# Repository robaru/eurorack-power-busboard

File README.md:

# Eurorack Power Busboard

A passive power busboard for a Eurorack case, based on the
[Eurorack Power Breakout](https://github.com/moPsy-project/eurorack-power-breakout) by Stefan Haun
(moPsy project). I took Stefan KiCad project as a starting point and started playing around with it
to create the busboard to power my modules.

* 10 Eurorack power headers (2×8, with +5V, CV and Gate)
* Power input on a 4-pin WAGO screw terminal (+12V, GND, -12V, +5V)
* Basic filtering on each rail (ferrite bead, 100n and 10u)
* One LED per rail (+12V, -12V, +5V)
* Through-hole parts only, 190 × 31 mm, two M3 mounting holes

## Status

I built it and it works. Some things might need correcting, mostly the position of a few parts and
labels, so check the layout!

I have some spare PCBs. If you want one, get in touch!

## Files

* `eurorack-power-breakout.kicad_pro` / `.kicad_sch` / `.kicad_pcb`: KiCad project
* `eurorack-power-breakout-gerbers.zip`: Gerbers and drill files, ready to upload to a PCB fab
* `plots/`: the same Gerbers and drill files, unzipped
* `images/`: 3D renders (`board-3d.png`, `board-top.png`)
* `eurorack-power-breakout.csv`: bill of materials

## License

Licensed under [Creative Commons Attribution-ShareAlike 4.0 International](http://creativecommons.org/licenses/by-sa/4.0/),
like the original. Original design by Stefan Haun (mail@tuxathome.de), modified by Roberto
Barumerli. See [LICENSE.txt](LICENSE.txt).

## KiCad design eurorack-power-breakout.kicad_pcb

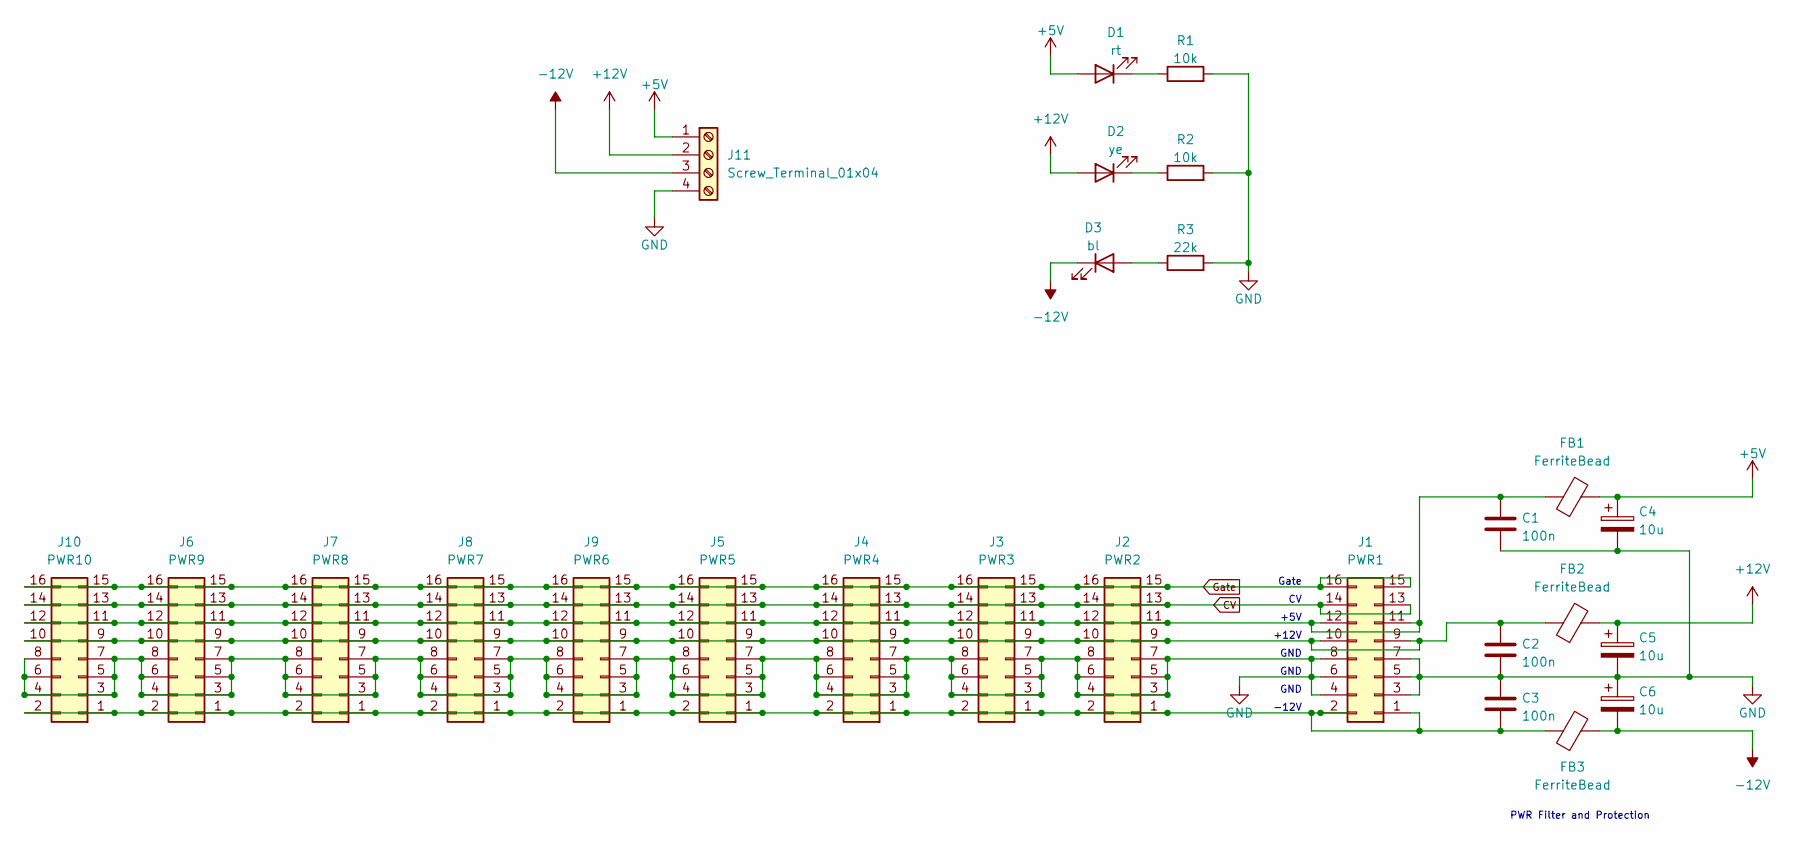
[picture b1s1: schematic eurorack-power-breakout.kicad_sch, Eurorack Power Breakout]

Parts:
C1, C2, C3: 100n; C_Disc_D4.3mm_W1.9mm_P5.00mm
C4, C5, C6: 10u; CP_Radial_D5.0mm_P2.50mm
D1: rt; LED_D3.0mm
D2: ye; LED_D3.0mm
D3: bl; LED_D3.0mm
FB1, FB2, FB3: FerriteBead; R_Axial_DIN0207_L6.3mm_D2.5mm_P7.62mm_Horizontal
J1: PWR1; PinHeader_2x08_P2.54mm_Vertical
J2: PWR2; PinHeader_2x08_P2.54mm_Vertical
J3: PWR3; PinHeader_2x08_P2.54mm_Vertical
J4: PWR4; PinHeader_2x08_P2.54mm_Vertical
J5: PWR5; PinHeader_2x08_P2.54mm_Vertical
J6: PWR9; PinHeader_2x08_P2.54mm_Vertical
J7: PWR8; PinHeader_2x08_P2.54mm_Vertical
J8: PWR7; PinHeader_2x08_P2.54mm_Vertical
J9: PWR6; PinHeader_2x08_P2.54mm_Vertical
J10: PWR10; PinHeader_2x08_P2.54mm_Vertical
J11: Screw_Terminal_01x04; TerminalBlock_WAGO_236-104_1x04_P5.00mm_45Degree
R1, R2: 10k; R_Axial_DIN0207_L6.3mm_D2.5mm_P2.54mm_Vertical
R3: 22k; R_Axial_DIN0207_L6.3mm_D2.5mm_P2.54mm_Vertical

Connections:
+5V: C4.1, D1.2 (A), FB1.2, J11.1
+12V: C5.1, D2.2 (A), FB2.2, J11.2
-12V: C6.2, D3.1 (K), FB3.2, J11.3
CV: J1.13, J1.14, J2.13, J2.14, J3.13, J3.14, J4.13, J4.14, J5.13, J5.14, J6.13, J6.14, J7.13, J7.14, J8.13, J8.14, J9.13, J9.14, J10.13, J10.14
GND: C1.2, C2.2, C3.1, C4.2, C5.2, C6.1, J1.3, J1.4, J1.5, J1.6, J1.7, J1.8, J2.3, J2.4, J2.5, J2.6, J2.7, J2.8, J3.3, J3.4, J3.5, J3.6, J3.7, J3.8, J4.3, J4.4, J4.5, J4.6, J4.7, J4.8, J5.3, J5.4, J5.5, J5.6, J5.7, J5.8, J6.3, J6.4, J6.5, J6.6, J6.7, J6.8, J7.3, J7.4, J7.5, J7.6, J7.7, J7.8, J8.3, J8.4, J8.5, J8.6, J8.7, J8.8, J9.3, J9.4, J9.5, J9.6, J9.7, J9.8, J10.3, J10.4, J10.5, J10.6, J10.7, J10.8, J11.4, R1.2, R2.2, R3.2
Gate: J1.15, J1.16, J2.15, J2.16, J3.15, J3.16, J4.15, J4.16, J5.15, J5.16, J6.15, J6.16, J7.15, J7.16, J8.15, J8.16, J9.15, J9.16, J10.15, J10.16
unnamed: D1.1 (K), R1.1
unnamed: D2.1 (K), R2.1
unnamed: D3.2 (A), R3.1
unnamed: C3.2, FB3.1, J1.1, J1.2, J2.1, J2.2, J3.1, J3.2, J4.1, J4.2, J5.1, J5.2, J6.1, J6.2, J7.1, J7.2, J8.1, J8.2, J9.1, J9.2, J10.1, J10.2
unnamed: C2.1, FB2.1, J1.9, J1.10, J2.9, J2.10, J3.9, J3.10, J4.9, J4.10, J5.9, J5.10, J6.9, J6.10, J7.9, J7.10, J8.9, J8.10, J9.9, J9.10, J10.9, J10.10
unnamed: C1.1, FB1.1, J1.11, J1.12, J2.11, J2.12, J3.11, J3.12, J4.11, J4.12, J5.11, J5.12, J6.11, J6.12, J7.11, J7.12, J8.11, J8.12, J9.11, J9.12, J10.11, J10.12

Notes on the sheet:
GND
+5V
Gate
+12V
-12V
PWR Filter and Protection

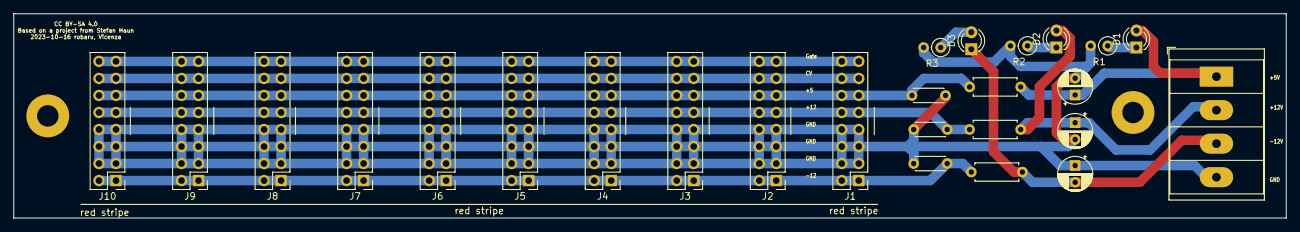
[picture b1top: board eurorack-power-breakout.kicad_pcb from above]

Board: 2 copper layers, 189.9 x 30.5 mm, 26 parts (0 on the bottom side), 12 nets.

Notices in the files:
eurorack-power-breakout.kicad_pcb:
CC BY-SA 4.0
